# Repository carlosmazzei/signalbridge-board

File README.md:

<!-- markdownlint-disable MD033 MD041 -->
<div align="center">

</div>
<!-- markdownlint-enable MD033 MD041 -->

# Signalbridge - Board

**A comprehensive, industrial-grade breakout board for the Raspberry Pi Pico with advanced I/O expansion and control capabilities.**

## Fabricated Board

<!-- markdownlint-disable MD033 -->

<!-- markdownlint-enable MD033 -->

## Overview

Signalbridge is a feature-rich breakout board designed to unlock the full potential of the Raspberry Pi Pico microcontroller. This board transforms the Pico into a powerful controller suitable for industrial automation, IoT projects, robotics, and educational applications.

> [!TIP]
> This board is designed for the Raspberry Pi Pico.

Related repos:

- [Signalbridge breakout board](https://github.com/carlosmazzei/signalbridge-board) (This repo)
- [Signalbridge test suite](https://github.com/carlosmazzei/signalbridge-test-suite)
- [Signalbridge firmware](https://github.com/carlosmazzei/signalbridge-controller)

### Key Highlights

- **Wide Input Voltage Range**: 4.2V to 18V DC input with efficient 3.3V/3A regulation
- **16-Channel Analog Inputs**: Expandable analog reading capability through integrated multiplexer
- **8×8 Keypad Matrix**: Professional keypad interface with ESD protection
- **Multiple Communication Interfaces**: I2C, UART, and 8 SPI outputs
- **LED Display Controller**: TM1639 for driving 7-segment displays and LED matrices
- **PWM Output**: Dedicated PWM output with 3-pin connector
- **User LED**: Power-on indicator LED
- **Mounting**: 4× mounting holes for secure installation
- **Comprehensive Protection**: ESD protection on all external interfaces
- **Professional Grade**: Designed for reliability and expandability

## Project Structure

```text
signalbridge-board/
├── pi_controller.kicad_{pro,sch,pcb,dru,prl}  # Main KiCad 9 project
├── fp-lib-table, sym-lib-table                # KiCad library tables
├── fabrication-toolkit-options.json           # Fabrication-Toolkit settings
├── library/                                   # Custom symbols & footprints
├── assets/                                    # Board renders & logos
├── datasheets/                                # Component datasheets (PDF)
├── jlcpcb/                                    # Fabrication outputs (gerbers, BOM, CPL)
└── docs/
    └── PRODUCTION_CHECKLIST.md                # PCBA production & test-point checklist
```

The `jlcpcb/` folder name is referenced by `.github/workflows/release_jlcpcb.yml`; the `library/` folder and the root `pi_controller.*` files are referenced by `fp-lib-table` / `sym-lib-table`. Renaming any of these will break the project.

## Features
### Power Management

- **Input Voltage**: 4.2V to 18V DC (via barrel jack connector)
- **Regulation**: AP62300TWU buck converter providing 3.3V at up to 3A
- **Efficiency**: High-efficiency switching regulator with low dropout
- **Protection**: Input protection and power indicator LED
- **Flexibility**: Can be powered via USB or external DC supply

### Analog Inputs (16-Channel)

- **Multiplexer**: CD74HC4067 16:1 analog multiplexer
- **Resolution**: 12-bit ADC resolution (0-4095 digital values)
- **Voltage Range**: 0V to 3.3V analog input range
- **Reference**: Precision LM4040DBZ-3 3.0V voltage reference for accuracy
- **Software Control**: Channel selection via GPIO control lines
- **Connectors**: 16× 3-pin screw terminals for easy field wiring

### Keypad Matrix Interface (8×8)

- **Matrix Size**: 8 rows × 8 columns (64 keys maximum)
- **Connectors**: 2× 16-pin IDC headers for row/column connections
- **Protection**: BAT54J Schottky diodes on every line for ESD protection
- **Pull-ups**: Integrated pull-up resistors for reliable scanning
- **Flexibility**: Supports various keypad sizes up to 8×8

### Communication Interfaces

#### I2C Interface

- **Pins**: SDA (GPIO2), SCL (GPIO3)
- **Pull-ups**: 2.2kΩ pull-up resistors to 3.3V
- **Connector**: 4-pin terminal block (VCC, GND, SDA, SCL)
- **Voltage**: 3.3V logic levels

#### UART Interface  

- **Pins**: TX (GPIO0), RX (GPIO1)
- **Connector**: 4-pin terminal block (VCC, GND, TX, RX)
- **Voltage**: 3.3V logic levels
- **Usage**: Serial communication, debugging, or external device control

#### SPI Interfaces (8 Outputs)

- **Outputs**: 8× independent SPI chip select lines
- **Connectors**: 6-pin headers per SPI output
- **Pinout**: VCC, GND, MOSI, MISO, SCLK, CS
- **Shared Bus**: Common MOSI, MISO, SCLK with individual chip selects
- **Applications**: Multiple SPI devices, sensor networks, display modules

### Display Controller

- **IC**: TM1639 LED display controller
- **Interface**: 3-wire serial (DIO, CLK, STB)
- **Capability**: Drive 8×8 LED matrix or multiple 7-segment displays
- **Features**: Built-in key scanning, adjustable brightness, minimal GPIO usage
- **Connector**: 6-pin header with standard TM1639 pinout

### Additional I/O

- **PWM Output**: Dedicated PWM output with 3-pin connector
- **Test Points**: Multiple test points for debugging and measurement
- **User LED**: Power-on indicator LED
- **Mounting**: 4× mounting holes for secure installation

## Technical Specifications

### Electrical Characteristics

| Parameter             | Min | Typ | Max  | Unit |
| --------------------- | --- | --- | ---- | ---- |
| Input Voltage         | 4.2 | 9.0 | 18.0 | V    |
| Output Voltage        | -   | 3.3 | -    | V    |
| Output Current        | -   | -   | 3.0  | A    |
| ADC Resolution        | -   | 12  | -    | bits |
| ADC Reference         | -   | 3.0 | -    | V    |
| Operating Temperature | -20 | 25  | 85   | °C   |

### Physical Dimensions

- **PCB Size**: 99.7 × 99.1 mm
- **Mounting Holes**: 4× M3 holes
- **Connector Types**: Screw terminals, pin headers, IDC connectors
- **Layer Count**: 4-layer PCB design

## Hardware Setup

### 1. Power Connection

- DC Input: Connect 4.2V to 18V DC to J2 barrel connector
- USB Power: Connect USB cable to Raspberry Pi Pico (alternative)

### 2. Analog Inputs (AN1-AN16)

- Signal Range: 0V to 3.3V maximum
- Connector: 3-pin screw terminals
- Pinout: Signal, VDDA, GND

### 3. Keypad Matrix

- Row Connector (JR1-JR8): Connect keypad rows 1-8
- Column Connector: Connect keypad columns 1-8
- Matrix Size: Up to 8×8 (64 keys)

### 4. Communication Interfaces

- I2C (J30): VCC(3.3V), GND, SDA, SCL
- UART (J31): VCC(3.3V), GND, TX, RX  
- SPI (JSPI1-JSPI7): VCC, GND, MOSI, MISO, SCLK, CS

## Assembly Instructions

### Required Components

- 1× Raspberry Pi Pico (with headers soldered)
- 1× Signalbridge PCB
- Connectors (screw terminals, pin headers as needed)
- Power supply (4.2V to 18V DC)

### Assembly Steps

1. **Inspect PCB**: Check for any manufacturing defects
2. **Install Raspberry Pi Pico**: Insert Pico into main socket (U4 position)
3. **Connect Power**: Wire DC supply to J2 barrel connector
4. **Test Power**: Verify 3.3V output and LED indicator
5. **Install Connectors**: Solder required connectors for your application
6. **Test Interfaces**: Verify I2C, SPI, and ADC functionality

### Troubleshooting

- **No Power LED**: Check input voltage and connections
- **ADC Readings Incorrect**: Verify voltage reference and input range
- **I2C Not Working**: Check pull-up resistors and wiring
- **Keypad Issues**: Verify matrix connections and ESD protection

## Pin Assignments

### Raspberry Pi Pico Pin Usage

| GPIO  | Function  | Description               |
| ----- | --------- | ------------------------- |
| 0     | UART0_TX  | UART transmit             |
| 1     | UART0_RX  | UART receive              |
| 2     | SDA       | I2C data line             |
| 3     | SCL       | I2C clock line            |
| 4-9   | ROW1-ROW6 | Keypad matrix rows        |
| 10    | ADC_MUX_A | ADC multiplexer control A |
| 11    | ADC_MUX_B | ADC multiplexer control B |
| 12    | ADC_MUX_C | ADC multiplexer control C |
| 13    | ADC_MUX_D | ADC multiplexer control D |
| 14-21 | COL1-COL8 | Keypad matrix columns     |
| 22    | PWM_OUT   | PWM output                |
| 26    | ADC0      | Multiplexed analog input  |
| 27    | CS_LED    | TM1639 strobe             |
| 28    | CS_KEY    | TM1639 data I/O           |

### SPI Chip Select Assignments

| Signal | GPIO   | Description  |
| ------ | ------ | ------------ |
| CS1    | GPIO5  | SPI device 1 |
| CS2    | GPIO6  | SPI device 2 |
| CS3    | GPIO7  | SPI device 3 |
| CS4    | GPIO8  | SPI device 4 |
| CS5    | GPIO9  | SPI device 5 |
| CS6    | GPIO16 | SPI device 6 |
| CS7    | GPIO17 | SPI device 7 |
| CS8    | GPIO18 | SPI device 8 |

### Shared SPI Signals

| Signal | GPIO   | Description              |
| ------ | ------ | ------------------------ |
| MOSI   | GPIO19 | SPI Master Out, Slave In |
| MISO   | GPIO20 | SPI Master In, Slave Out |
| SCLK   | GPIO21 | SPI Clock                |

## Safety and Compliance

### Electrical Safety

- Input voltage: 4.2V to 18V DC only
- Maximum current: 3A output
- ESD protection: BAT54J diodes on all external interfaces
- Reverse polarity: Protected by input diode

### Usage Guidelines

- Do not exceed maximum input voltage (18V)
- Ensure proper grounding for all analog measurements
- Use appropriate wire gauge for current requirements
- Follow proper ESD handling procedures

## License

This project is released under the [**CERN Open Hardware Licence**](LICENSE).

## Contributing

We welcome contributions to improve Signalbridge! Here's how you can help:

### Hardware Improvements

- PCB layout optimizations
- Additional connector options
- Component substitutions for better availability
- Cost reduction improvements

### Software Development

- Additional driver libraries
- Example projects
- Documentation improvements
- Bug fixes and optimizations

### How to Contribute

1. Fork the repository
2. Create a feature branch (`git checkout -b feature/amazing-feature`)
3. Commit your changes (`git commit -m 'Add amazing feature'`)
4. Push to the branch (`git push origin feature/amazing-feature`)
5. Open a Pull Request

### Issue Reporting

Please use GitHub Issues to report:

- Hardware design problems
- Software bugs
- Documentation errors
- Feature requests

## Support

### Community Support

- **GitHub Issues**: Report bugs and request features
- **Discussions**: General questions and project sharing
- **Wiki**: Community-maintained documentation

### Documentation

- **Schematic**: Detailed circuit diagrams
- **PCB Layout**: Layer stackup and routing
- **Assembly Guide**: Step-by-step assembly instructions
- **User Manual**: Comprehensive usage guide

## Acknowledgments

- **Raspberry Pi Foundation** for the excellent Pico microcontroller
- **KiCad Development Team** for the outstanding PCB design tools
- **Open Source Community** for inspiration and shared knowledge
- **Component Manufacturers** for detailed datasheets and application notes

## Roadmap

### Version 2.0 Features (Planned)

- [ ] USB-C connector option
- [ ] CAN bus interface

### Long-term Goals

- [ ] Industrial enclosure design
- [ ] DIN rail mounting option
- [ ] Higher current power supply (5A)
- [ ] Isolated I/O options
- [ ] Professional certification (CE, FCC)

---

Made with care for the maker community

Signalbridge - Expanding the possibilities of Raspberry Pi Pico

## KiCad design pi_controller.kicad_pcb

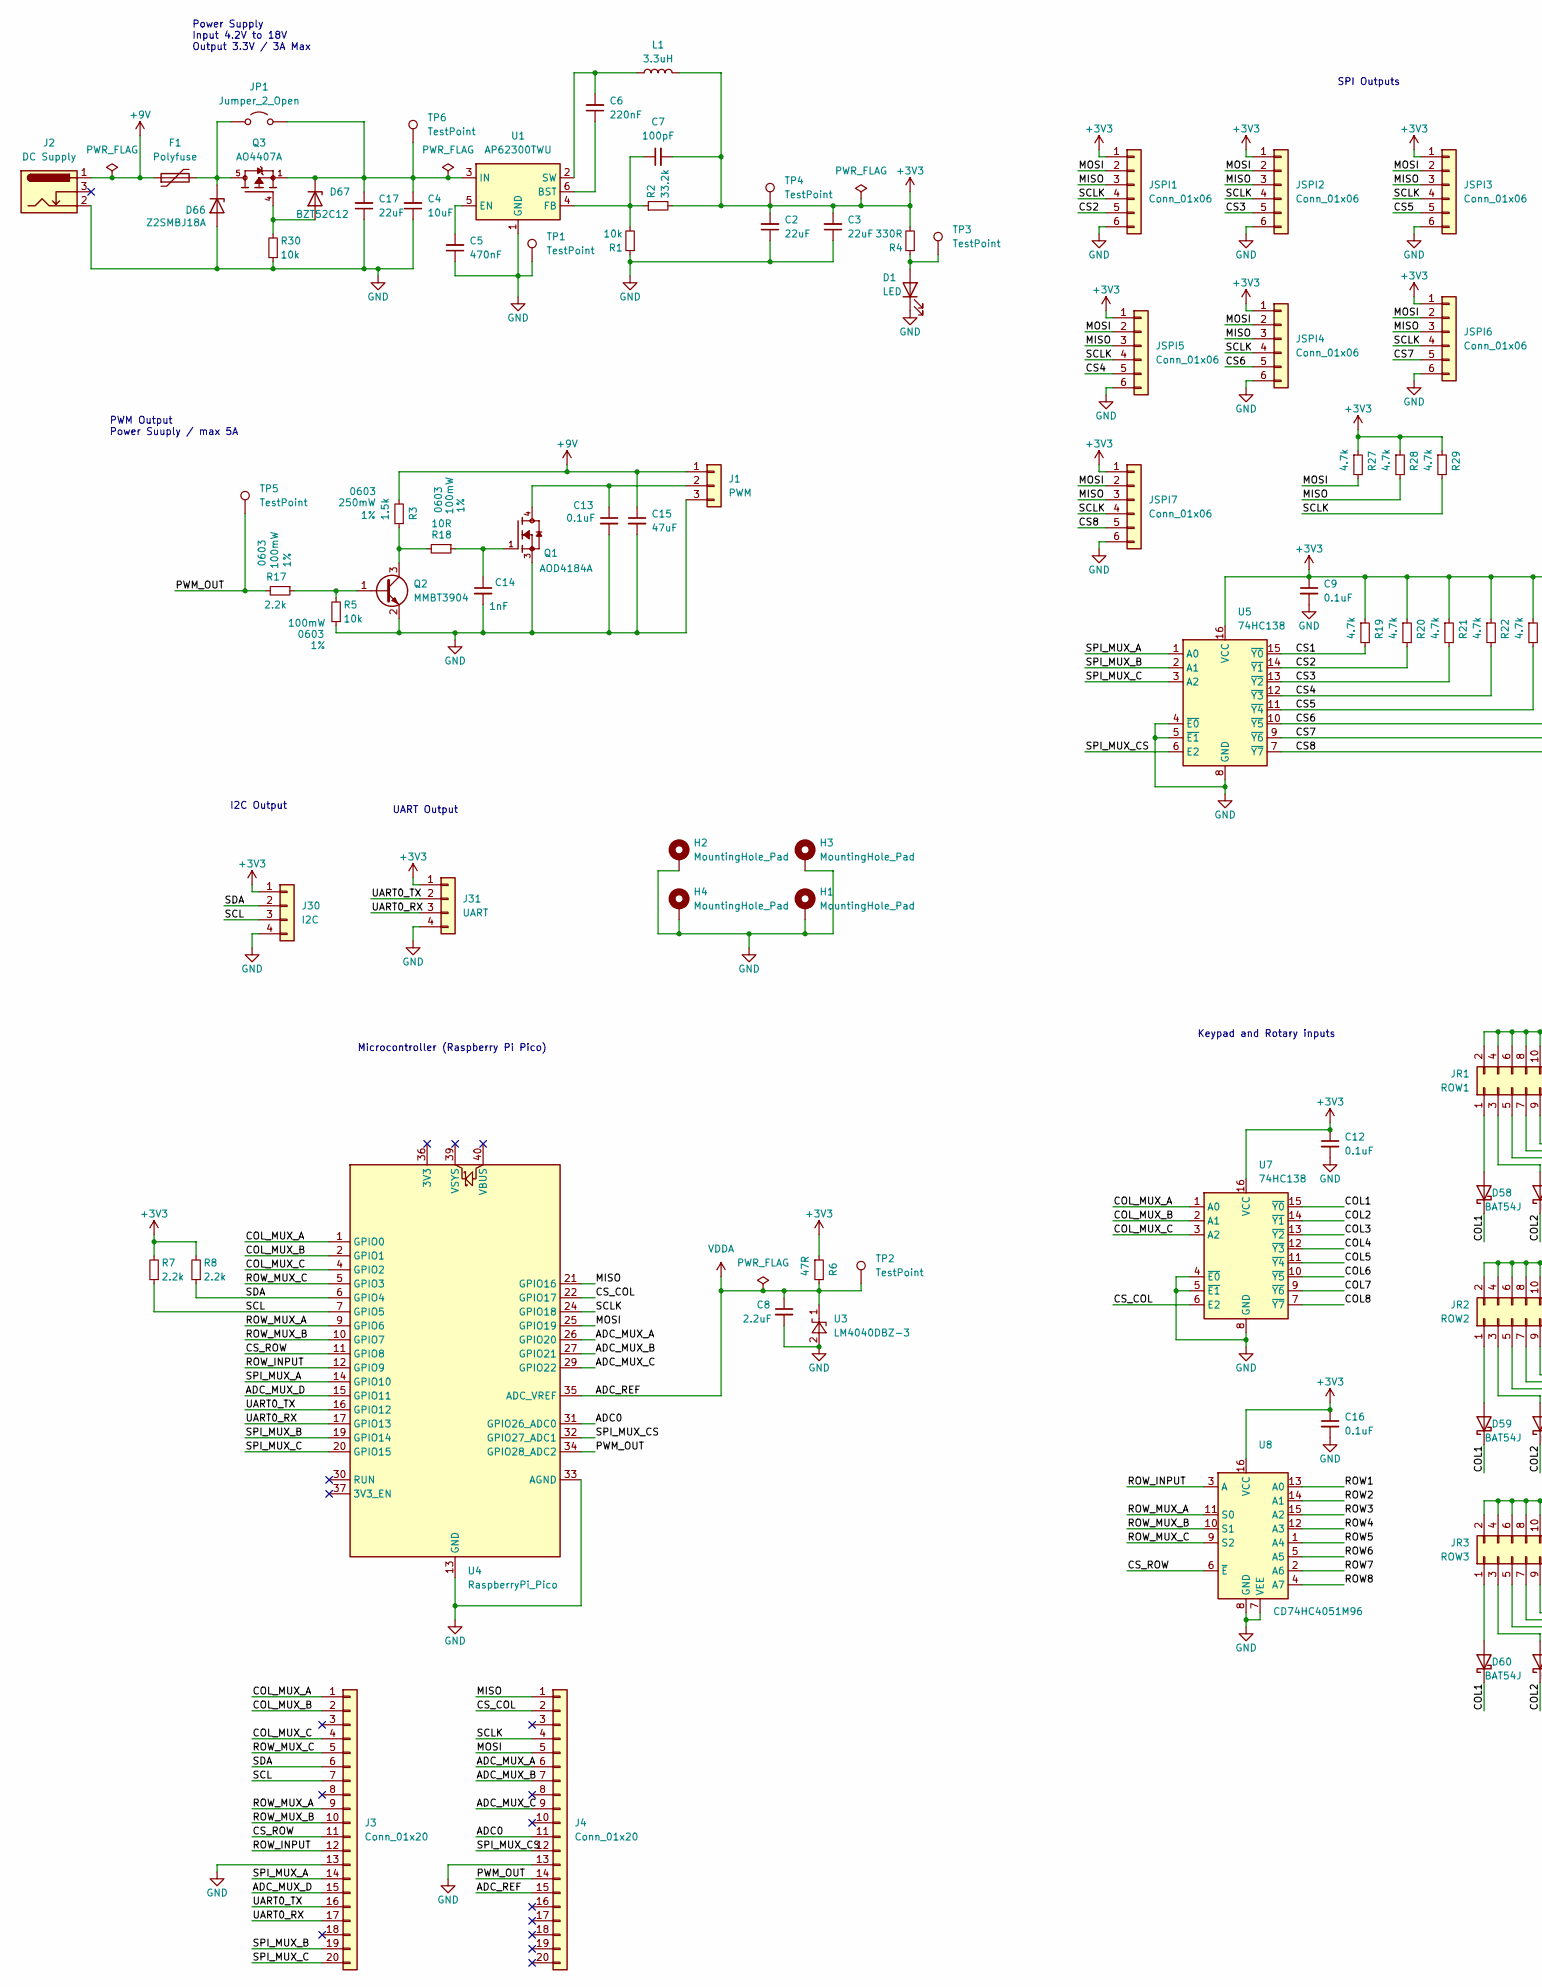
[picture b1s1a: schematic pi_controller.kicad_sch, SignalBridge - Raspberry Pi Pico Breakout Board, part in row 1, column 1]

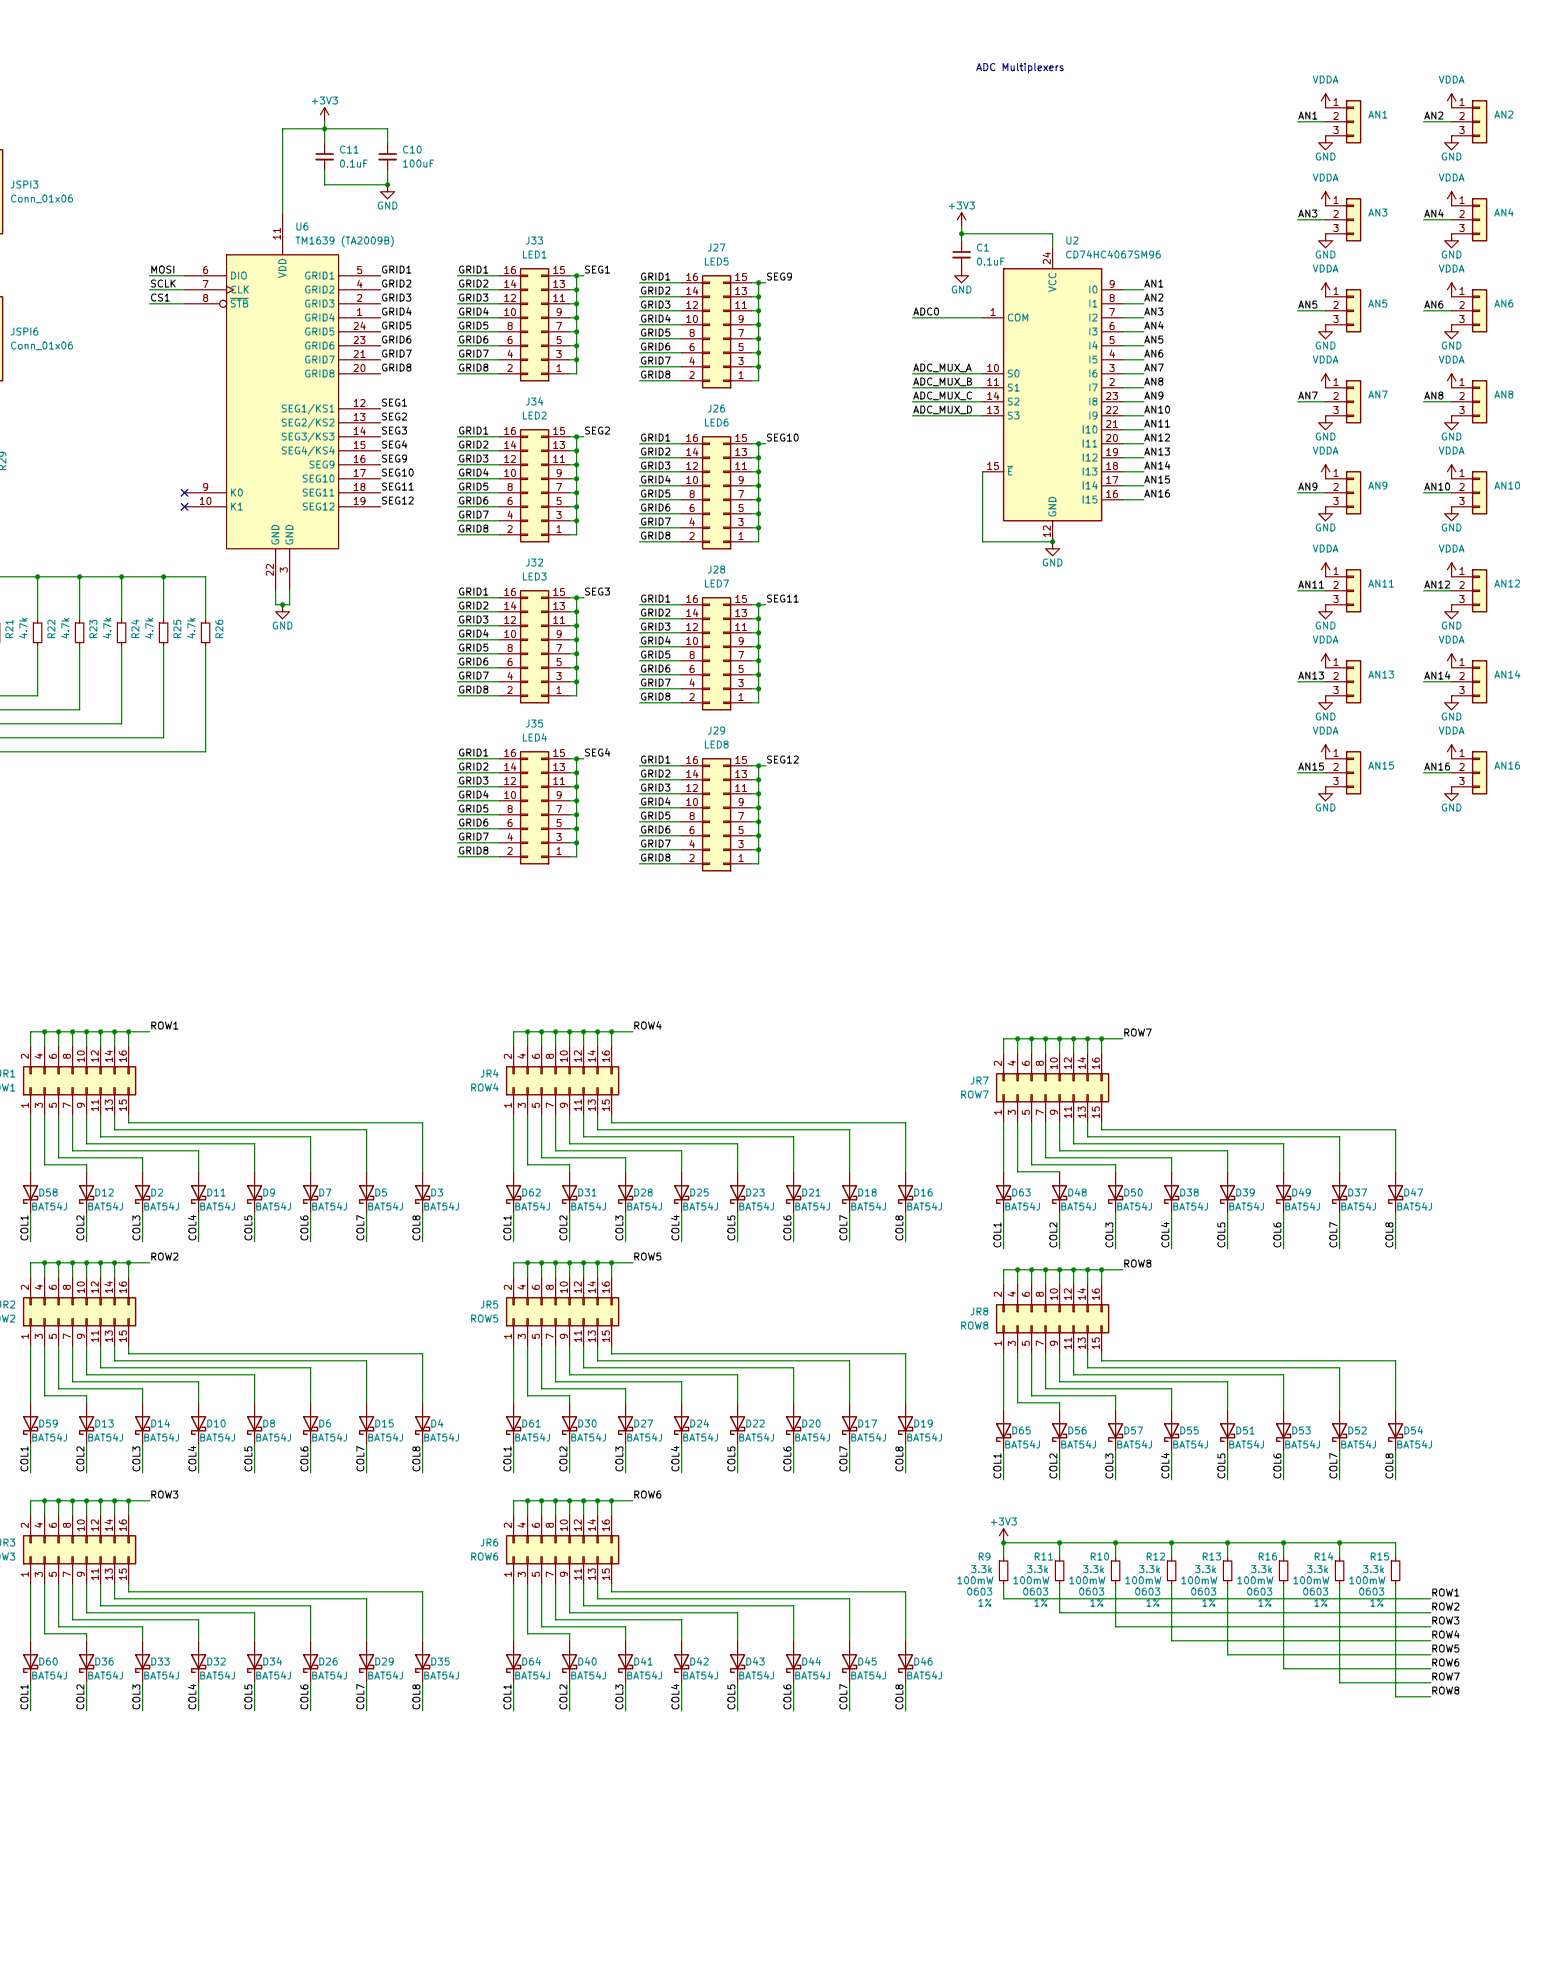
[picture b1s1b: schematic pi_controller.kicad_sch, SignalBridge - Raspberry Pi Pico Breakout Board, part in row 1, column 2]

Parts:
AN1: AN1; JST_ZH_B3B-ZR_1x03_P1.50mm_Vertical_SilkSafe; LCSC PN C495558
AN2: AN2; JST_ZH_B3B-ZR_1x03_P1.50mm_Vertical_SilkSafe; LCSC PN C495558
AN3: AN3; JST_ZH_B3B-ZR_1x03_P1.50mm_Vertical_SilkSafe; LCSC PN C495558
AN4: AN4; JST_ZH_B3B-ZR_1x03_P1.50mm_Vertical_SilkSafe; LCSC PN C495558
AN5: AN5; JST_ZH_B3B-ZR_1x03_P1.50mm_Vertical_SilkSafe; LCSC PN C495558
AN6: AN6; JST_ZH_B3B-ZR_1x03_P1.50mm_Vertical_SilkSafe; LCSC PN C495558
AN7: AN7; JST_ZH_B3B-ZR_1x03_P1.50mm_Vertical_SilkSafe; LCSC PN C495558
AN8: AN8; JST_ZH_B3B-ZR_1x03_P1.50mm_Vertical_SilkSafe; LCSC PN C495558
AN9: AN9; JST_ZH_B3B-ZR_1x03_P1.50mm_Vertical_SilkSafe; LCSC PN C495558
AN10: AN10; JST_ZH_B3B-ZR_1x03_P1.50mm_Vertical_SilkSafe; LCSC PN C495558
AN11: AN11; JST_ZH_B3B-ZR_1x03_P1.50mm_Vertical_SilkSafe; LCSC PN C495558
AN12: AN12; JST_ZH_B3B-ZR_1x03_P1.50mm_Vertical_SilkSafe; LCSC PN C495558
AN13: AN13; JST_ZH_B3B-ZR_1x03_P1.50mm_Vertical_SilkSafe; LCSC PN C495558
AN14: AN14; JST_ZH_B3B-ZR_1x03_P1.50mm_Vertical_SilkSafe; LCSC PN C495558
AN15: AN15; JST_ZH_B3B-ZR_1x03_P1.50mm_Vertical_SilkSafe; LCSC PN C495558
AN16: AN16; JST_ZH_B3B-ZR_1x03_P1.50mm_Vertical_SilkSafe; LCSC PN C495558
C1, C11, C12, C16: 0.1uF; C_0603_1608Metric_Pad1.08x0.95mm_HandSolder; Voltage Rating 50V; Tolerance 10%; LCSC PN C14663
C2, C3, C17: 22uF; C_1206_3216Metric_Pad1.33x1.80mm_HandSolder; Temperature Rating X5R; Tolerance 10%; LCSC PN C12891
C4: 10uF; C_1206_3216Metric_Pad1.33x1.80mm_HandSolder; Voltage Rating 50V; Tolerance 10%; LCSC PN C13585
C5: 470nF; C_0603_1608Metric_Pad1.08x0.95mm_HandSolder; Voltage Rating 25V; Tolerance 10%; LCSC PN C1623
C6: 220nF; C_0603_1608Metric_Pad1.08x0.95mm_HandSolder; Tolerance 10%; Voltage Rating 25V; LCSC PN C21120
C7: 100pF; C_0603_1608Metric_Pad1.08x0.95mm_HandSolder; Tolerance 10%; Voltage Rating 50V; LCSC PN C14858
C8: 2.2uF; C_0603_1608Metric_Pad1.08x0.95mm_HandSolder; Voltage Rating 16V; Tolerance 10%; LCSC PN C23630
C9: 0.1uF; C_0603_1608Metric_Pad1.08x0.95mm_HandSolder; Tolerance 5%; Voltage Rating 50V; LCSC PN C14663
C10: 100uF; C_1206_3216Metric_Pad1.33x1.80mm_HandSolder; Voltage Rating 50V; Tolerance 10%; LCSC PN C15008
C13: 0.1uF; C_0603_1608Metric_Pad1.08x0.95mm_HandSolder; Tolerance 10%; Voltage Rating 50V; LCSC PN C14663
C14: 1nF; C_0603_1608Metric_Pad1.08x0.95mm_HandSolder; Tolerance 10%; Voltage Rating 50V; LCSC PN C1588
C15: 47uF; C_1206_3216Metric_Pad1.33x1.80mm_HandSolder; Voltage Rating 25V; Tolerance 10%; LCSC PN C76659
D1: LED; LED_0805_2012Metric_Pad1.15x1.40mm_HandSolder; LCSC PN C2297
D2, D3, D4, D5, D6, D7, D8, D9, D10, D11, D12, D13, D14, D15, D16, D17, D18, D19, D20, D21, D22, D23, D24, D25, D26, D27, D28, D29, D30, D31, D32, D33, D34, D35, D36, D37, D38, D39, D40, D41, D42, D43, D44, D45, D46, D47, D48, D49, D50, D51, D52, D53, D54, D55, D56, D57, D58, D59, D60, D61, D62, D63, D64, D65: BAT54J; D_SOD-323F; LCSC PN C358488
D66: Z2SMBJ18A; D_SMB; LCSC PN C10212
D67: BZT52C12; D_SOD-123; LCSC PN C19077410
F1: Polyfuse; Fuse_1210_3225Metric_Pad1.42x2.65mm_HandSolder; LCSC PN C22379947
H1, H2, H3, H4: MountingHole_Pad; MountingHole_2.2mm_M2_ISO14580_Pad_TopBottom
J1: PWM; JST_ZH_B3B-ZR_1x03_P1.50mm_Vertical_SilkSafe; LCSC PN C495558
J2: DC Supply; BarrelJack_Horizontal; LCSC PN C381116
J3, J4: Conn_01x20; PinSocket_1x20_P2.54mm_Vertical; LCSC PN C5224030
J26: LED6; PinHeader_2x08_P2.54mm_Vertical; LCSC PN C68234
J27: LED5; PinHeader_2x08_P2.54mm_Vertical; LCSC PN C68234
J28: LED7; PinHeader_2x08_P2.54mm_Vertical; LCSC PN C68234
J29: LED8; PinHeader_2x08_P2.54mm_Vertical; LCSC PN C68234
J30: I2C; JST_ZH_B4B-ZR_1x04_P1.50mm_Vertical_SilkSafe; LCSC PN C163034
J31: UART; JST_ZH_B4B-ZR_1x04_P1.50mm_Vertical_SilkSafe; LCSC PN C163034
J32: LED3; PinHeader_2x08_P2.54mm_Vertical; LCSC PN C68234
J33: LED1; PinHeader_2x08_P2.54mm_Vertical; LCSC PN C68234
J34: LED2; PinHeader_2x08_P2.54mm_Vertical; LCSC PN C68234
J35: LED4; PinHeader_2x08_P2.54mm_Vertical; LCSC PN C68234
JP1: Jumper_2_Open; SolderJumper-2_P1.3mm_Open_TrianglePad1.0x1.5mm_Silk
JR1: ROW1; PinHeader_2x08_P2.54mm_Vertical; LCSC PN C68234
JR2: ROW2; PinHeader_2x08_P2.54mm_Vertical; LCSC PN C68234
JR3: ROW3; PinHeader_2x08_P2.54mm_Vertical; LCSC PN C68234
JR4: ROW4; PinHeader_2x08_P2.54mm_Vertical; LCSC PN C68234
JR5: ROW5; PinHeader_2x08_P2.54mm_Vertical; LCSC PN C68234
JR6: ROW6; PinHeader_2x08_P2.54mm_Vertical; LCSC PN C68234
JR7: ROW7; PinHeader_2x08_P2.54mm_Vertical; LCSC PN C68234
JR8: ROW8; PinHeader_2x08_P2.54mm_Vertical; LCSC PN C68234
JSPI1, JSPI2, JSPI3, JSPI4, JSPI5, JSPI6, JSPI7: Conn_01x06; JST_ZH_B6B-ZR_1x06_P1.50mm_Vertical_SilkSafe; LCSC PN C495631
L1: 3.3uH; L_Sunlord_MWSA0604S; Tolerance 20%; LCSC PN C5189747
Q1: AOD4184A; DPAK228P994X240-4N; PARTREV 0; LCSC PN C99124
Q2: MMBT3904; SOT-23; LCSC PN C20526
Q3: AO4407A; SOIC127P600X175-8N; PARTREV I
R1, R5, R30: 10k; R_0603_1608Metric_Pad0.98x0.95mm_HandSolder; Tolerance 1%; LCSC PN C25804
R2: 33.2k; R_0603_1608Metric_Pad0.98x0.95mm_HandSolder; Tolerance 1%; LCSC PN C23003
R3: 1.5k; R_0603_1608Metric_Pad0.98x0.95mm_HandSolder; Tolerance 1%; LCSC PN C543357
R4: 330R; R_0603_1608Metric_Pad0.98x0.95mm_HandSolder; Tolerance 1%; LCSC PN C23138
R6: 47R; R_0603_1608Metric_Pad0.98x0.95mm_HandSolder; Tolerance 1%; LCSC PN C23182
R7, R8, R17: 2.2k; R_0603_1608Metric_Pad0.98x0.95mm_HandSolder; Tolerance 1%; LCSC PN C4190
R9, R10, R11, R12, R13, R14, R15, R16: 3.3k; R_0603_1608Metric_Pad0.98x0.95mm_HandSolder; Tolerance 1%; LCSC PN C22978
R18: 10R; R_0603_1608Metric_Pad0.98x0.95mm_HandSolder; Tolerance 1%; LCSC PN C22859
R19, R20, R21, R22, R23, R24, R25, R26, R27, R28, R29: 4.7k; R_0603_1608Metric_Pad0.98x0.95mm_HandSolder; Tolerance 1%; LCSC PN C23162
TP1, TP2, TP3, TP4, TP5, TP6: TestPoint; TestPoint_Pad_D2.0mm
U1: AP62300TWU; TSOT-23-6; LCSC PN C1883519
U2: CD74HC4067SM96; SSOP-24_5.3x8.2mm_P0.65mm; LCSC PN C98457
U3: LM4040DBZ-3; SOT-23; LCSC PN C460608
U4: RaspberryPi_Pico; RaspberryPi_Pico_Common_THT_CustomSilk
U5, U7: 74HC138; SOIC-16_3.9x9.9mm_P1.27mm; LCSC PN C6818
U6: TM1639 (TA2009B); SOP-24_7.5x15.4mm_P1.27mm; LCSC PN C20611984
U8: CD74HC4051M96; SOIC-16_3.9x9.9mm_P1.27mm; LCSC PN C132065

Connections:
+3V3: C1.1, C2.2, C3.2, C7.2, C9.1, C10.1, C11.1, C12.1, C16.1, J30.1, J31.1, JSPI1.1, JSPI2.1, JSPI3.1, JSPI4.1, JSPI5.1, JSPI6.1, JSPI7.1, L1.2, R2.2, R4.2, R6.1, R7.2, R8.2, R9.1, R10.1, R11.1, R12.1, R13.1, R14.1, R15.1, R16.1, R19.1, R20.1, R21.1, R22.1, R23.1, R24.1, R25.1, R26.1, R27.1, R28.1, R29.1, TP4.1, U2.24 (VCC), U5.16 (VCC), U6.11 (VDD), U7.16 (VCC), U8.16 (VCC)
+9V: C15.1, F1.1, J1.1, J2.1, R3.2
/ADC0: J4.11, U2.1 (COM), U4.31 (GPIO26_ADC0)
/ADC_MUX_A: J4.6, U2.10 (S0), U4.26 (GPIO20)
/ADC_MUX_B: J4.7, U2.11 (S1), U4.27 (GPIO21)
/ADC_MUX_C: J4.9, U2.14 (S2), U4.29 (GPIO22)
/ADC_MUX_D: J3.15, U2.13 (S3), U4.15 (GPIO11)
/AN1: AN1.2, U2.9 (I0)
/AN2: AN2.2, U2.8 (I1)
/AN3: AN3.2, U2.7 (I2)
/AN4: AN4.2, U2.6 (I3)
/AN5: AN5.2, U2.5 (I4)
/AN6: AN6.2, U2.4 (I5)
/AN7: AN7.2, U2.3 (I6)
/AN8: AN8.2, U2.2 (I7)
/AN9: AN9.2, U2.23 (I8)
/AN10: AN10.2, U2.22 (I9)
/AN11: AN11.2, U2.21 (I10)
/AN12: AN12.2, U2.20 (I11)
/AN13: AN13.2, U2.19 (I12)
/AN14: AN14.2, U2.18 (I13)
/AN15: AN15.2, U2.17 (I14)
/AN16: AN16.2, U2.16 (I15)
/COL1: D58.1 (K), D59.1 (K), D60.1 (K), D61.1 (K), D62.1 (K), D63.1 (K), D64.1 (K), D65.1 (K), U7.15 (~Y0)
/COL2: D12.1 (K), D13.1 (K), D30.1 (K), D31.1 (K), D36.1 (K), D40.1 (K), D48.1 (K), D56.1 (K), U7.14 (~Y1)
/COL3: D2.1 (K), D14.1 (K), D27.1 (K), D28.1 (K), D33.1 (K), D41.1 (K), D50.1 (K), D57.1 (K), U7.13 (~Y2)
/COL4: D10.1 (K), D11.1 (K), D24.1 (K), D25.1 (K), D32.1 (K), D38.1 (K), D42.1 (K), D55.1 (K), U7.12 (~Y3)
/COL5: D8.1 (K), D9.1 (K), D22.1 (K), D23.1 (K), D34.1 (K), D39.1 (K), D43.1 (K), D51.1 (K), U7.11 (~Y4)
/COL6: D6.1 (K), D7.1 (K), D20.1 (K), D21.1 (K), D26.1 (K), D44.1 (K), D49.1 (K), D53.1 (K), U7.10 (~Y5)
/COL7: D5.1 (K), D15.1 (K), D17.1 (K), D18.1 (K), D29.1 (K), D37.1 (K), D45.1 (K), D52.1 (K), U7.9 (~Y6)
/COL8: D3.1 (K), D4.1 (K), D16.1 (K), D19.1 (K), D35.1 (K), D46.1 (K), D47.1 (K), D54.1 (K), U7.7 (~Y7)
/COL_MUX_A: J3.1, U4.1 (GPIO0), U7.1 (A0)
/COL_MUX_B: J3.2, U4.2 (GPIO1), U7.2 (A1)
/COL_MUX_C: J3.4, U4.4 (GPIO2), U7.3 (A2)
/CS1: R19.2, U5.15 (~Y0), U6.8 (~STB)
/CS2: JSPI1.5, R20.2, U5.14 (~Y1)
/CS3: JSPI2.5, R21.2, U5.13 (~Y2)
/CS4: JSPI5.5, R22.2, U5.12 (~Y3)
/CS5: JSPI3.5, R23.2, U5.11 (~Y4)
/CS6: JSPI4.5, R24.2, U5.10 (~Y5)
/CS7: JSPI6.5, R25.2, U5.9 (~Y6)
/CS8: JSPI7.5, R26.2, U5.7 (~Y7)
/CS_COL: J4.2, U4.22 (GPIO17), U7.6 (E2)
/CS_ROW: J3.11, U4.11 (GPIO8), U8.6 (~E)
/GRID1: J26.16, J27.16, J28.16, J29.16, J32.16, J33.16, J34.16, J35.16, U6.5 (GRID1)
/GRID2: J26.14, J27.14, J28.14, J29.14, J32.14, J33.14, J34.14, J35.14, U6.4 (GRID2)
/GRID3: J26.12, J27.12, J28.12, J29.12, J32.12, J33.12, J34.12, J35.12, U6.2 (GRID3)
/GRID4: J26.10, J27.10, J28.10, J29.10, J32.10, J33.10, J34.10, J35.10, U6.1 (GRID4)
/GRID5: J26.8, J27.8, J28.8, J29.8, J32.8, J33.8, J34.8, J35.8, U6.24 (GRID5)
/GRID6: J26.6, J27.6, J28.6, J29.6, J32.6, J33.6, J34.6, J35.6, U6.23 (GRID6)
/GRID7: J26.4, J27.4, J28.4, J29.4, J32.4, J33.4, J34.4, J35.4, U6.21 (GRID7)
/GRID8: J26.2, J27.2, J28.2, J29.2, J32.2, J33.2, J34.2, J35.2, U6.20 (GRID8)
/MISO: J4.1, JSPI1.3, JSPI2.3, JSPI3.3, JSPI4.3, JSPI5.3, JSPI6.3, JSPI7.3, R28.2, U4.21 (GPIO16)
/MOSI: J4.5, JSPI1.2, JSPI2.2, JSPI3.2, JSPI4.2, JSPI5.2, JSPI6.2, JSPI7.2, R27.2, U4.25 (GPIO19), U6.6 (DIO)
/PWM_OUT: J4.14, R17.2, TP5.1, U4.34 (GPIO28_ADC2)
/ROW1: JR1.2, JR1.4, JR1.6, JR1.8, JR1.10, JR1.12, JR1.14, JR1.16, R9.2, U8.13 (A0)
/ROW2: JR2.2, JR2.4, JR2.6, JR2.8, JR2.10, JR2.12, JR2.14, JR2.16, R11.2, U8.14 (A1)
/ROW3: JR3.2, JR3.4, JR3.6, JR3.8, JR3.10, JR3.12, JR3.14, JR3.16, R10.2, U8.15 (A2)
/ROW4: JR4.2, JR4.4, JR4.6, JR4.8, JR4.10, JR4.12, JR4.14, JR4.16, R12.2, U8.12 (A3)
/ROW5: JR5.2, JR5.4, JR5.6, JR5.8, JR5.10, JR5.12, JR5.14, JR5.16, R13.2, U8.1 (A4)
/ROW6: JR6.2, JR6.4, JR6.6, JR6.8, JR6.10, JR6.12, JR6.14, JR6.16, R16.2, U8.5 (A5)
/ROW7: JR7.2, JR7.4, JR7.6, JR7.8, JR7.10, JR7.12, JR7.14, JR7.16, R14.2, U8.2 (A6)
/ROW8: JR8.2, JR8.4, JR8.6, JR8.8, JR8.10, JR8.12, JR8.14, JR8.16, R15.2, U8.4 (A7)
/ROW_INPUT: J3.12, U4.12 (GPIO9), U8.3 (A)
/ROW_MUX_A: J3.9, U4.9 (GPIO6), U8.11 (S0)
/ROW_MUX_B: J3.10, U4.10 (GPIO7), U8.10 (S1)
/ROW_MUX_C: J3.5, U4.5 (GPIO3), U8.9 (S2)
/SCL: J3.7, J30.3, R7.1, U4.7 (GPIO5)
/SCLK: J4.4, JSPI1.4, JSPI2.4, JSPI3.4, JSPI4.4, JSPI5.4, JSPI6.4, JSPI7.4, R29.2, U4.24 (GPIO18), U6.7 (CLK)
/SDA: J3.6, J30.2, R8.1, U4.6 (GPIO4)
/SEG1: J33.1, J33.3, J33.5, J33.7, J33.9, J33.11, J33.13, J33.15, U6.12 (SEG1/KS1)
/SEG2: J34.1, J34.3, J34.5, J34.7, J34.9, J34.11, J34.13, J34.15, U6.13 (SEG2/KS2)
/SEG3: J32.1, J32.3, J32.5, J32.7, J32.9, J32.11, J32.13, J32.15, U6.14 (SEG3/KS3)
/SEG4: J35.1, J35.3, J35.5, J35.7, J35.9, J35.11, J35.13, J35.15, U6.15 (SEG4/KS4)
/SEG9: J27.1, J27.3, J27.5, J27.7, J27.9, J27.11, J27.13, J27.15, U6.16 (SEG9)
/SEG10: J26.1, J26.3, J26.5, J26.7, J26.9, J26.11, J26.13, J26.15, U6.17 (SEG10)
/SEG11: J28.1, J28.3, J28.5, J28.7, J28.9, J28.11, J28.13, J28.15, U6.18 (SEG11)
/SEG12: J29.1, J29.3, J29.5, J29.7, J29.9, J29.11, J29.13, J29.15, U6.19 (SEG12)
/SPI_MUX_A: J3.14, U4.14 (GPIO10), U5.1 (A0)
/SPI_MUX_B: J3.19, U4.19 (GPIO14), U5.2 (A1)
/SPI_MUX_C: J3.20, U4.20 (GPIO15), U5.3 (A2)
/SPI_MUX_CS: J4.12, U4.32 (GPIO27_ADC1), U5.6 (E2)
/UART0_RX: J3.17, J31.3, U4.17 (GPIO13)
/UART0_TX: J3.16, J31.2, U4.16 (GPIO12)
GND: AN1.3, AN2.3, AN3.3, AN4.3, AN5.3, AN6.3, AN7.3, AN8.3, AN9.3, AN10.3, AN11.3, AN12.3, AN13.3, AN14.3, AN15.3, AN16.3, C1.2, C2.1, C3.1, C4.1, C5.1, C8.2, C9.2, C10.2, C11.2, C12.2, C13.2, C14.2, C15.2, C16.2, C17.1, D1.1 (K), D66.2 (A), H1.1, H2.1, H3.1, H4.1, J1.3, J2.2, J3.13, J4.13, J30.4, J31.4, JSPI1.6, JSPI2.6, JSPI3.6, JSPI4.6, JSPI5.6, JSPI6.6, JSPI7.6, Q1.3, Q2.2 (E), R1.1, R5.1, R30.1, TP1.1, U1.1 (GND), U2.12 (GND), U2.15 (~E), U3.2 (A), U4.3 (GND), U4.8 (GND), U4.13 (GND), U4.18 (GND), U4.23 (GND), U4.28 (GND), U4.33 (AGND), U4.38 (GND), U5.4 (~E0), U5.5 (~E1), U5.8 (GND), U6.3 (GND), U6.22 (GND), U7.4 (~E0), U7.5 (~E1), U7.8 (GND), U8.7 (VEE), U8.8 (GND)
unnamed: C14.1, Q1.1, R18.1
unnamed: D1.2 (A), R4.1, TP3.1
unnamed: D2.2 (A), JR1.5
unnamed: D3.2 (A), JR1.15
unnamed: D4.2 (A), JR2.15
unnamed: D5.2 (A), JR1.13
unnamed: D6.2 (A), JR2.11
unnamed: D7.2 (A), JR1.11
unnamed: D8.2 (A), JR2.9
unnamed: D9.2 (A), JR1.9
unnamed: D10.2 (A), JR2.7
unnamed: D11.2 (A), JR1.7
unnamed: D12.2 (A), JR1.3
unnamed: D13.2 (A), JR2.3
unnamed: D14.2 (A), JR2.5
unnamed: D15.2 (A), JR2.13
unnamed: D16.2 (A), JR4.15
unnamed: D17.2 (A), JR5.13
unnamed: D18.2 (A), JR4.13
unnamed: D19.2 (A), JR5.15
unnamed: D20.2 (A), JR5.11
unnamed: D21.2 (A), JR4.11
unnamed: D22.2 (A), JR5.9
unnamed: D23.2 (A), JR4.9
unnamed: D24.2 (A), JR5.7
unnamed: D25.2 (A), JR4.7
unnamed: D26.2 (A), JR3.11
unnamed: D27.2 (A), JR5.5
unnamed: D28.2 (A), JR4.5
unnamed: D29.2 (A), JR3.13
unnamed: D30.2 (A), JR5.3
unnamed: D31.2 (A), JR4.3
unnamed: D32.2 (A), JR3.7
unnamed: D33.2 (A), JR3.5
unnamed: D34.2 (A), JR3.9
unnamed: D35.2 (A), JR3.15
unnamed: D36.2 (A), JR3.3
unnamed: D37.2 (A), JR7.13
unnamed: D38.2 (A), JR7.7
unnamed: D39.2 (A), JR7.9
unnamed: D40.2 (A), JR6.3
unnamed: D41.2 (A), JR6.5
unnamed: D42.2 (A), JR6.7
unnamed: D43.2 (A), JR6.9
unnamed: D44.2 (A), JR6.11
unnamed: D45.2 (A), JR6.13
unnamed: D46.2 (A), JR6.15
unnamed: D47.2 (A), JR7.15
unnamed: D48.2 (A), JR7.3
unnamed: D49.2 (A), JR7.11
unnamed: D50.2 (A), JR7.5
unnamed: D51.2 (A), JR8.9
unnamed: D52.2 (A), JR8.13
unnamed: D53.2 (A), JR8.11
unnamed: D54.2 (A), JR8.15
unnamed: D55.2 (A), JR8.7
unnamed: D56.2 (A), JR8.3
unnamed: D57.2 (A), JR8.5
unnamed: D58.2 (A), JR1.1
unnamed: D59.2 (A), JR2.1
unnamed: D60.2 (A), JR3.1
unnamed: D61.2 (A), JR5.1
unnamed: D62.2 (A), JR4.1
unnamed: D63.2 (A), JR7.1
unnamed: D64.2 (A), JR6.1
unnamed: D65.2 (A), JR8.1
unnamed: D66.1 (K), F1.2, JP1.1 (A), Q3.5, Q3.6, Q3.7, Q3.8
unnamed: D67.2 (A), Q3.4, R30.2
unnamed: C4.2, C17.2, D67.1 (K), JP1.2 (B), Q3.1, Q3.2, Q3.3, TP6.1, U1.3 (IN)
unnamed: C13.1, J1.2, Q1.4
unnamed: Q2.1 (B), R5.2, R17.1
unnamed: Q2.3 (C), R3.1, R18.2
unnamed: C6.1, U1.6 (BST)
unnamed: C5.2, U1.5 (EN)
unnamed: C7.1, R1.2, R2.1, U1.4 (FB)
unnamed: C6.2, L1.1, U1.2 (SW)
VDDA: AN1.1, AN2.1, AN3.1, AN4.1, AN5.1, AN6.1, AN7.1, AN8.1, AN9.1, AN10.1, AN11.1, AN12.1, AN13.1, AN14.1, AN15.1, AN16.1, C8.1, J4.15, R6.2, TP2.1, U3.1 (K), U4.35 (ADC_VREF)

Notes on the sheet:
UART Output
I2C Output
Microcontroller (Raspberry Pi Pico)
Keypad and Rotary inputs
SPI Outputs
PWM Output Power Suuply / max 5A
ADC Multiplexers
Power Supply Input 4.2V to 18V Output 3.3V / 3A Max

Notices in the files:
README.md:
License: CERN
